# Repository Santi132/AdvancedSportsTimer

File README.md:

# AdvancedSportsTimer
Advanced Sports Timer, software code and hardware designs. As done by Santiago Gutierrez, Cristian Velasquez, and Patrick Tchassem

Published under GPLv3

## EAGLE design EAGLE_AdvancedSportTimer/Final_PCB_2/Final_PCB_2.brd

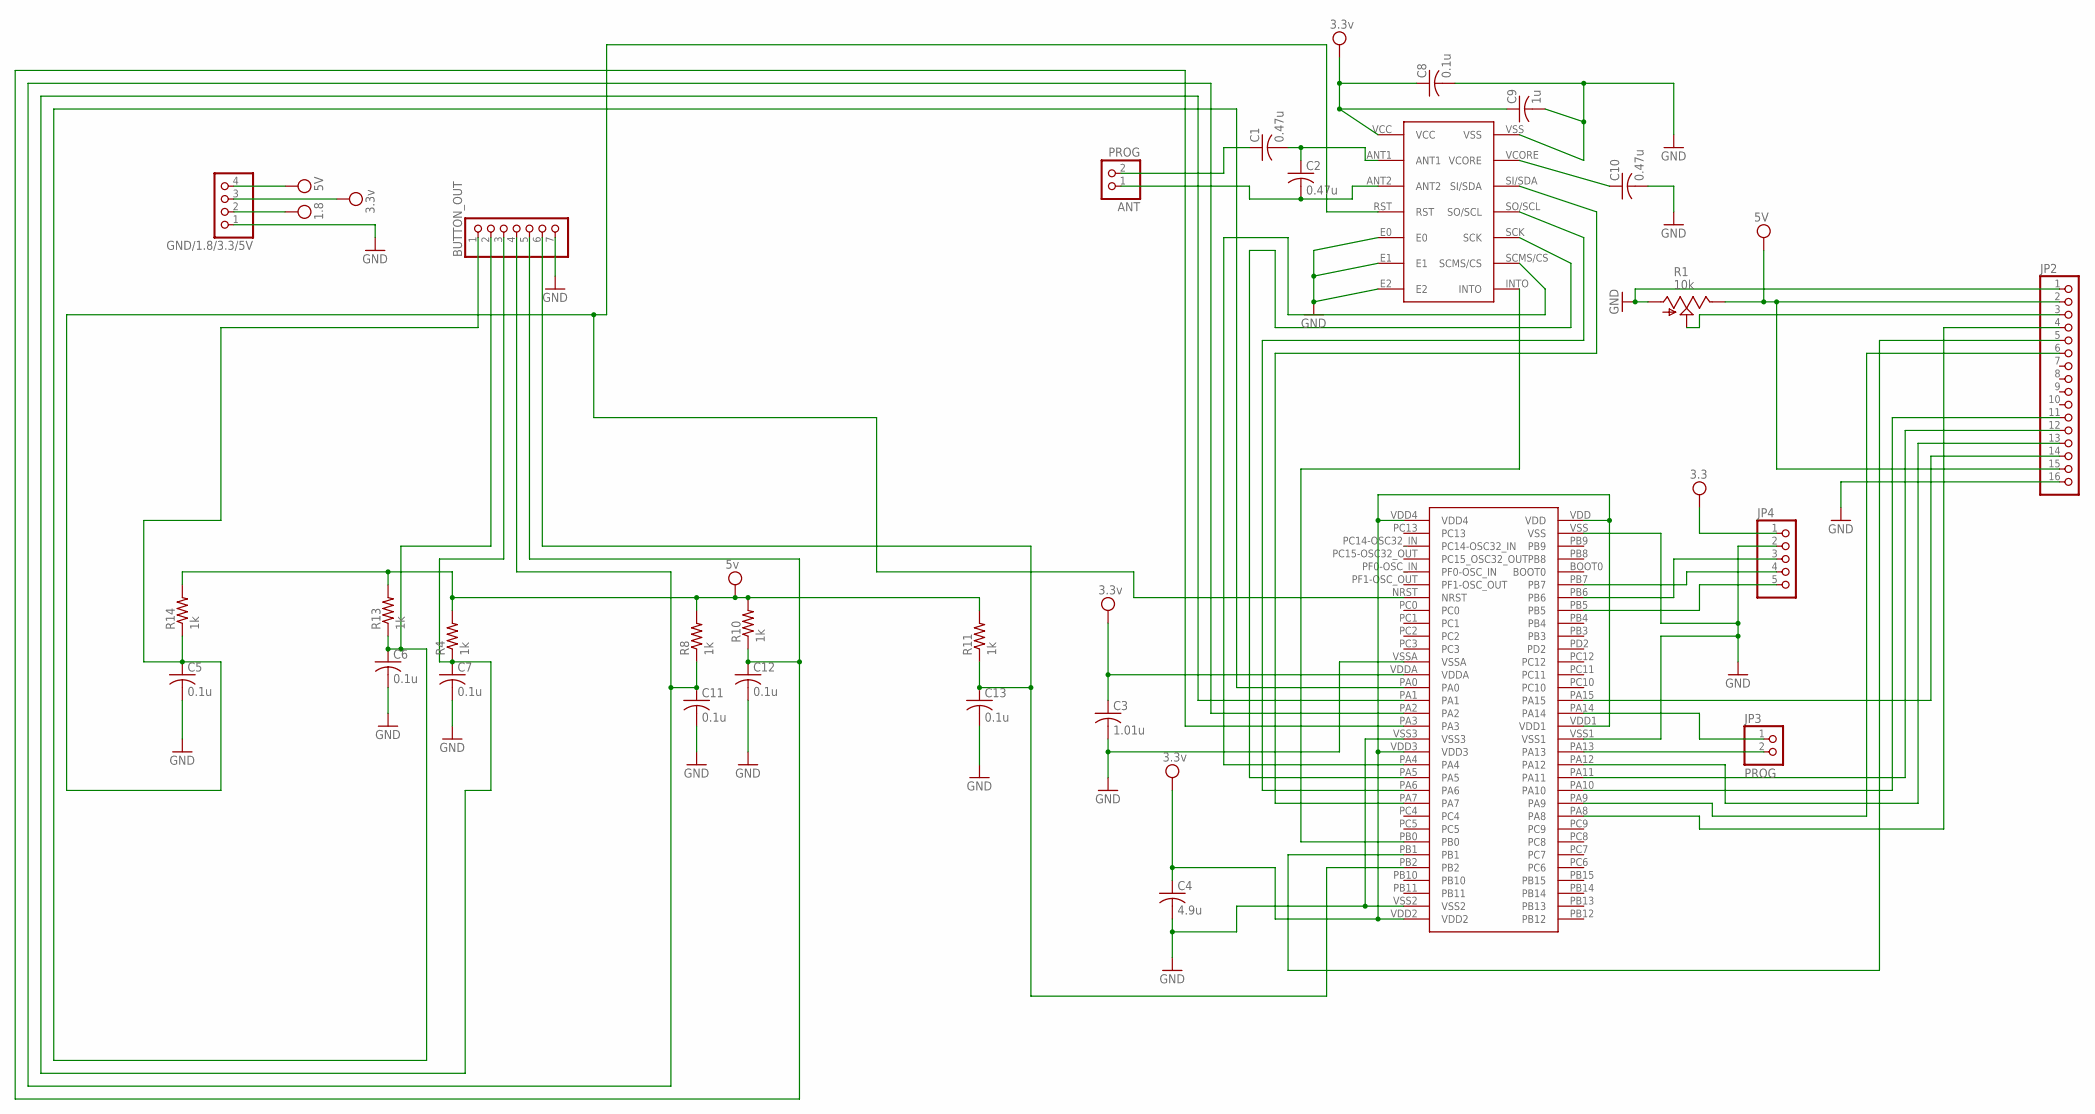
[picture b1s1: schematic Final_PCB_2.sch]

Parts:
ANT: PROG; 1X02
BUTTON_OUT: PINHD-1X7; 1X07
C1, C2, C10: 0.47u; C0805
C3: 1.01u; C0805
C4: 4.9u; C0805
C5, C6, C7, C8, C11, C12, C13: 0.1u; C0805
C9: 1u; C0805
GND/1.8/3.3/5V: PINHD-1X4/90; 1X04/90
JP2: PINHD-1X16; 1X16
JP3: PROG; 1X02
JP4: PINHD-1X5; 1X05
R1: 10k; B64Y
R4, R8, R10, R11, R13, R14: 1k; R0805
U$2: LQFP64
U$7: RF430CL330H

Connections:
GND: BUTTON_OUT.7, C3.2, C4.2, C5.2, C6.2, C7.2, C8.2, C9.2, C10.2, C11.2, C12.2, C13.2, GND/1.8/3.3/5V.1, JP2.1, JP2.16, JP4.2, R1.A, U$2.VSS, U$2.VSS1, U$2.VSS2, U$2.VSS3, U$2.VSSA, U$7.E0, U$7.E1, U$7.E2, U$7.VSS
unnamed: U$2.PB0, U$7.INTO
unnamed: U$2.PA5, U$7.SCK
unnamed: U$2.PA6, U$7.SO/SCL
unnamed: U$2.PA7, U$7.SI/SDA
unnamed: JP2.5, U$2.PB1
unnamed: ANT.1, C2.2, U$7.ANT2
unnamed: U$2.PA4, U$7.SCMS/CS
unnamed: C1.2, C2.1, U$7.ANT1
unnamed: BUTTON_OUT.3, C7.1, R4.1, U$2.PA1
unnamed: ANT.2, C1.1
unnamed: C10.1, U$7.VCORE
unnamed: JP2.3, R1.S
unnamed: JP2.4, U$2.PA8
unnamed: JP2.6, U$2.PA9
unnamed: JP2.11, U$2.PA10
unnamed: JP2.12, U$2.PA11
unnamed: JP2.13, U$2.PA12
unnamed: JP2.14, U$2.PA15
unnamed: BUTTON_OUT.5, C12.1, R10.1, U$2.PA3
unnamed: BUTTON_OUT.4, C11.1, R8.1, U$2.PA2
unnamed: JP3.1, U$2.PA14
unnamed: JP4.5, U$2.PB5
unnamed: JP4.3, U$2.PB6
unnamed: BUTTON_OUT.6, C13.1, R11.1, U$2.PB2
unnamed: BUTTON_OUT.1, C5.1, R14.1, U$2.NRST, U$7.RST
unnamed: BUTTON_OUT.2, C6.1, R13.1, U$2.PA0
unnamed: JP4.4, U$2.PB7
SWDIO: JP3.2, U$2.PA13
VCC: C3.1, C4.1, C8.1, C9.1, GND/1.8/3.3/5V.3, JP4.1, U$2.VDD, U$2.VDD1, U$2.VDD2, U$2.VDD3, U$2.VDD4, U$2.VDDA, U$7.VCC
VDD: GND/1.8/3.3/5V.4, JP2.2, JP2.15, R1.E, R4.2, R8.2, R10.2, R11.2, R13.2, R14.2
VEE: GND/1.8/3.3/5V.2

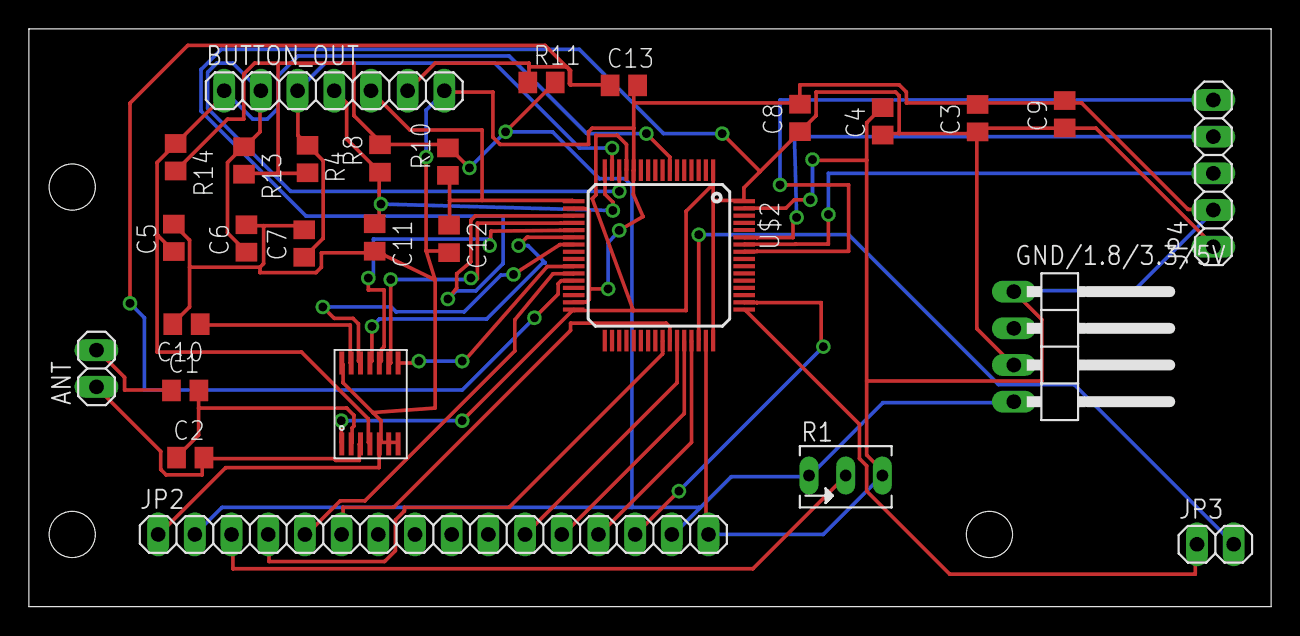
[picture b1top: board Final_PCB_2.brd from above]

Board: 2 copper layers, 86.0 x 40.0 mm, 28 parts (0 on the bottom side), 31 nets.

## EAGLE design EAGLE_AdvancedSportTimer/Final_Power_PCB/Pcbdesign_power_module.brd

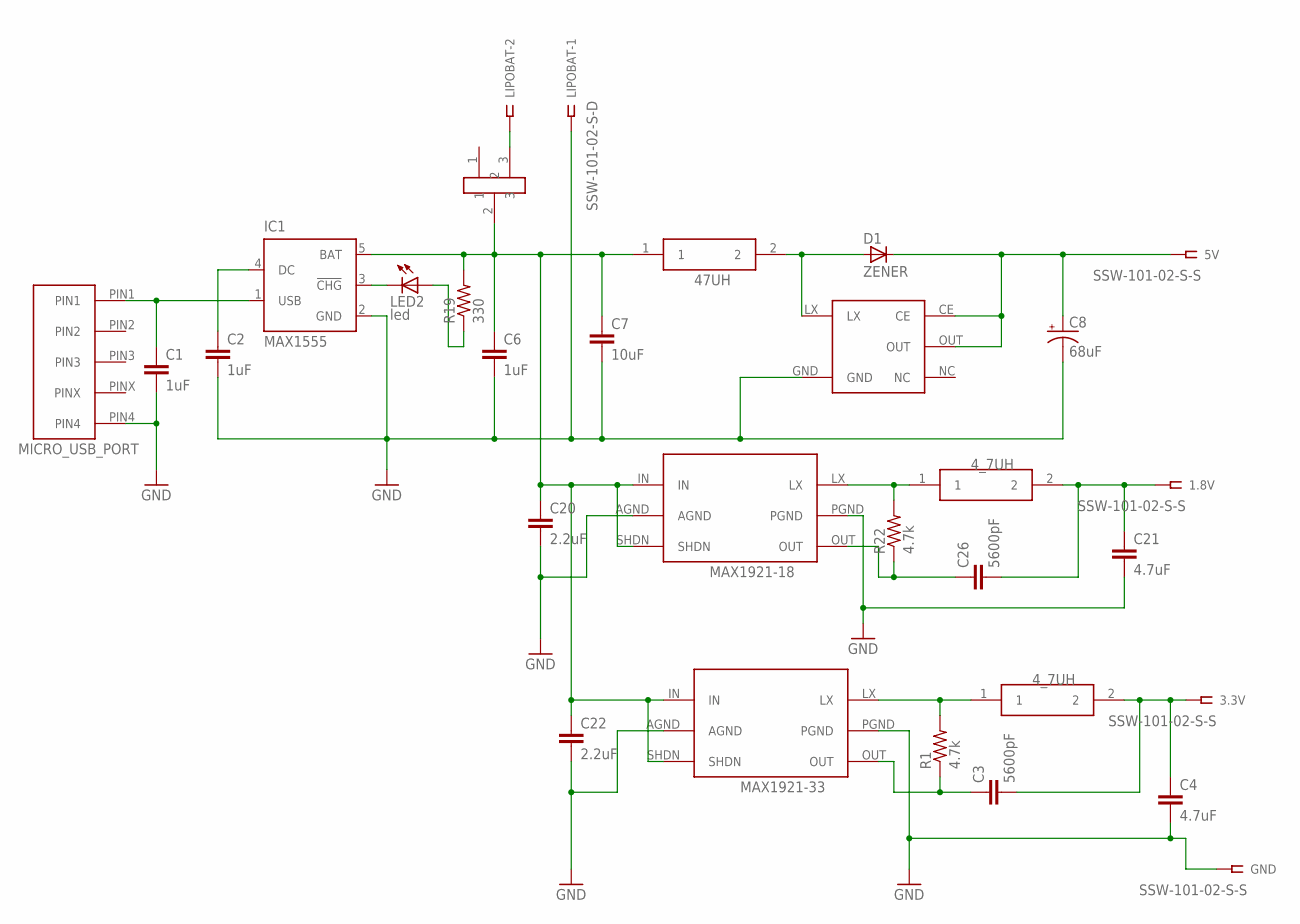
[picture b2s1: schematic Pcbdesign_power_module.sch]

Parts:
1.8V, 3.3V, 5V: SSW-101-02-S-S
10UH: SUMIDA_10U
C1, C2, C6: 1uF; C0805K
C3, C26: 5600pF; C0805K
C4, C21: 4.7uF; C0805K
C7: 10uF; C0805K
C8: 68uF; C/6032-28R
C20, C22: 2.2uF; C0805K
D1: ZENER; SOD123
GND: SSW-101-02-S-S
IC1: MAX1555; SOT23-5L
LED2: led; CHIPLED_0603
LIPOBAT: SSW-101-02-S-D
MAX1920, MAX1921-18: MAX1921
MICRO_USB: 10118192
R1, R22: 4.7k; R0805
R19: 330; R0805
U$1, U$2: SUMIDA_4.7U
U$3: NPC1402
U$4: SWITCH111

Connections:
GND: C1.2, C2.2, C4.2, C6.2, C7.2, C8.-, C20.2, C21.2, C22.2, GND.1, IC1.2 (GND), LIPOBAT.1, MAX1920.AGND, MAX1920.PGND, MAX1921-18.AGND, MAX1921-18.PGND, MICRO_USB.PIN4, U$3.GND
unnamed: C1.1, IC1.1 (USB), MICRO_USB.PIN1
unnamed: 5V.1, C8.+, D1.1 (C), U$3.CE, U$3.OUT
unnamed: IC1.3 (!CHG), LED2.C
unnamed: LED2.A, R19.1
unnamed: MAX1920.LX, R1.2, U$2.1
unnamed: LIPOBAT.2, U$4.3
unnamed: 1.8V.1, C21.1, C26.2, U$1.2
unnamed: MAX1921-18.LX, R22.2, U$1.1
unnamed: C26.1, MAX1921-18.OUT, R22.1
unnamed: 3.3V.1, C3.2, C4.1, U$2.2
unnamed: C3.1, MAX1920.OUT, R1.1
unnamed: 10UH.2, D1.2 (A), U$3.LX
unnamed: C2.1, IC1.4 (DC)
unnamed: 10UH.1, C6.1, C7.1, C20.1, C22.1, IC1.5 (BAT), MAX1920.IN, MAX1920.SHDN, MAX1921-18.IN, MAX1921-18.SHDN, R19.2, U$4.2

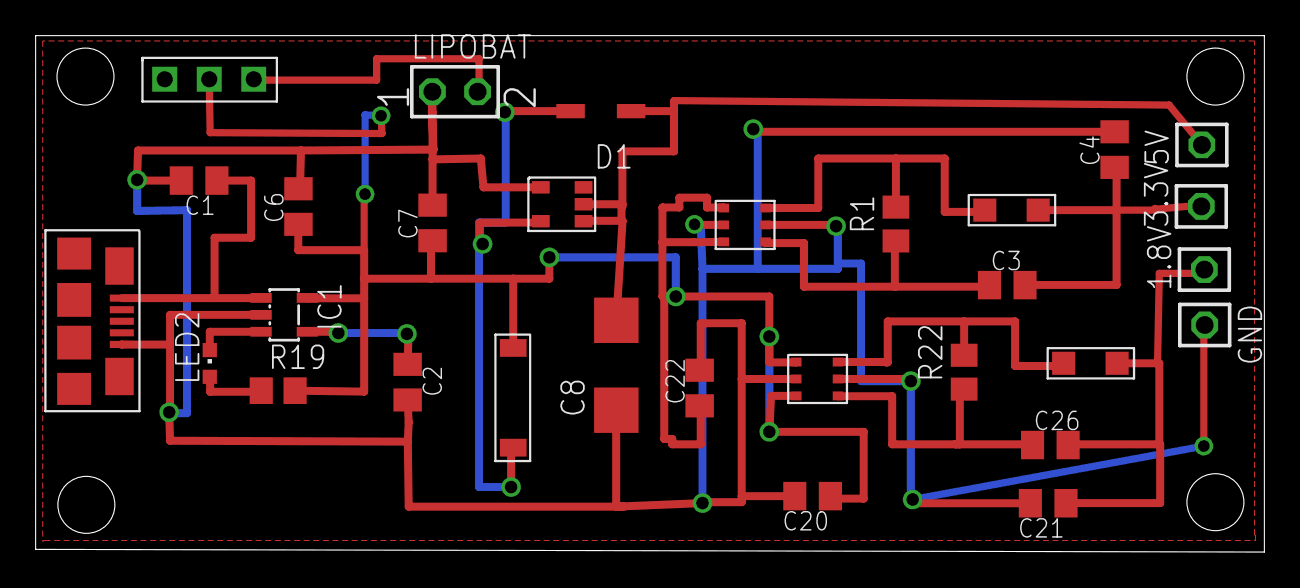
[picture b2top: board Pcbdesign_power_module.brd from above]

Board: 2 copper layers, 69.0 x 29.0 mm, 30 parts (0 on the bottom side), 15 nets.

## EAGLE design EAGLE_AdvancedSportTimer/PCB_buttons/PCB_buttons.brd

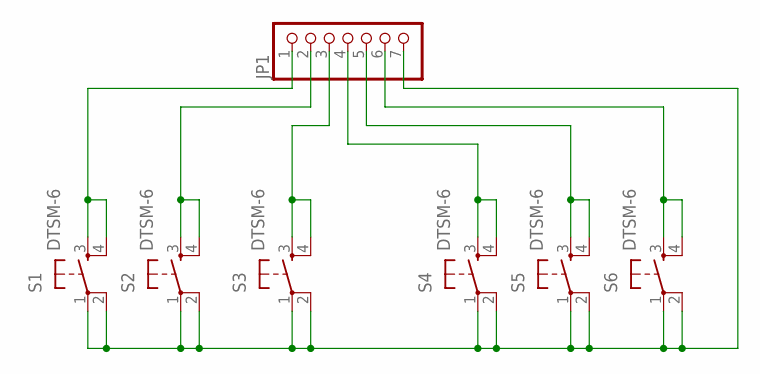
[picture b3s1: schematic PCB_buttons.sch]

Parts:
JP1: PINHD-1X7; 1X07
S1, S2, S3, S4, S5, S6: DTSM-6

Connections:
unnamed: JP1.7, S1.1, S1.2, S2.1, S2.2, S3.1, S3.2, S4.1, S4.2, S5.1, S5.2, S6.1, S6.2
unnamed: JP1.6, S6.3, S6.4
unnamed: JP1.5, S5.3, S5.4
unnamed: JP1.4, S4.3, S4.4
unnamed: JP1.3, S3.3, S3.4
unnamed: JP1.2, S2.3, S2.4
unnamed: JP1.1, S1.3, S1.4

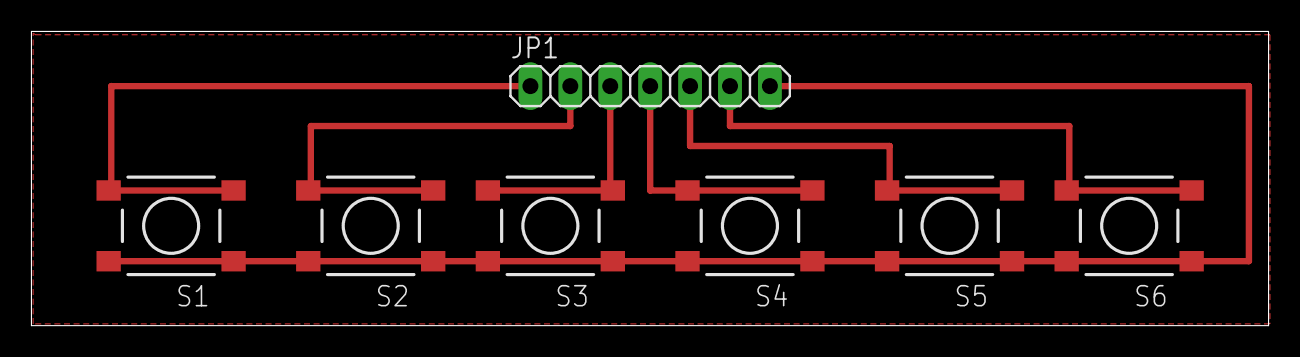
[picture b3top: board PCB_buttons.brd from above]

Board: 2 copper layers, 78.7 x 18.7 mm, 7 parts (0 on the bottom side), 7 nets.

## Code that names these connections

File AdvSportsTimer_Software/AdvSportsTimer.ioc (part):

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Mcu.Name=STM32F030RCTx
Mcu.Package=LQFP64
Mcu.UserName=STM32F030RCTx
PA10.Signal=GPIO_Output
PA11.Signal=GPIO_Output
PA12.Signal=GPIO_Output
PA13.Mode=Serial_Wire
PA13.Signal=SYS_SWDIO
PA14.Mode=Serial_Wire
PA14.Signal=SYS_SWCLK
PA15.Signal=GPIO_Output
PA8.Signal=GPIO_Output
PA9.Signal=GPIO_Output
PB1.Signal=GPIO_Output
board=AdvSportsTimer

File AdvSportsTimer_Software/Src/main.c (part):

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  HAL_GPIO_WritePin(GPIOA, GPIO_PIN_8|GPIO_PIN_9|GPIO_PIN_10|GPIO_PIN_11 
                          |GPIO_PIN_12|GPIO_PIN_15 | GPIO_PIN_4, GPIO_PIN_RESET);

  /*Configure GPIO pin : PB1 */
  GPIO_InitStruct.Pin = GPIO_PIN_1;
  GPIO_InitStruct.Mode = GPIO_MODE_OUTPUT_PP;
  GPIO_InitStruct.Pull = GPIO_NOPULL;
  GPIO_InitStruct.Speed = GPIO_SPEED_FREQ_HIGH;
  HAL_GPIO_Init(GPIOB, &GPIO_InitStruct);
	
	/*Configure GPIO pin : PB0 */
  GPIO_InitStruct.Pin = GPIO_PIN_0;
  GPIO_InitStruct.Mode = GPIO_MODE_INPUT;
  GPIO_InitStruct.Pull = GPIO_NOPULL;
  HAL_GPIO_Init(GPIOB, &GPIO_InitStruct);

  /*Configure GPIO pins : PA8 PA9 PA10 PA11 
                           PA12 PA15 PA4 */
  GPIO_InitStruct.Pin = GPIO_PIN_4 | GPIO_PIN_8|GPIO_PIN_9|GPIO_PIN_10|GPIO_PIN_11 
                          |GPIO_PIN_12|GPIO_PIN_15;
  GPIO_InitStruct.Mode = GPIO_MODE_OUTPUT_PP;
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
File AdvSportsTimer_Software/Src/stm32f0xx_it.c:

/**
  ******************************************************************************
  * @file    stm32f0xx_it.c
  * @brief   Interrupt Service Routines.
  ******************************************************************************
  *
  * COPYRIGHT(c) 2017 STMicroelectronics
  *
  * Redistribution and use in source and binary forms, with or without modification,
  * are permitted provided that the following conditions are met:
  *   1. Redistributions of source code must retain the above copyright notice,
  *      this list of conditions and the following disclaimer.
  *   2. Redistributions in binary form must reproduce the above copyright notice,
  *      this list of conditions and the following disclaimer in the documentation
  *      and/or other materials provided with the distribution.
  *   3. Neither the name of STMicroelectronics nor the names of its contributors
  *      may be used to endorse or promote products derived from this software
  *      without specific prior written permission.
  *
  * THIS SOFTWARE IS PROVIDED BY THE COPYRIGHT HOLDERS AND CONTRIBUTORS "AS IS"
  * AND ANY EXPRESS OR IMPLIED WARRANTIES, INCLUDING, BUT NOT LIMITED TO, THE
  * IMPLIED WARRANTIES OF MERCHANTABILITY AND FITNESS FOR A PARTICULAR PURPOSE ARE
  * DISCLAIMED. IN NO EVENT SHALL THE COPYRIGHT HOLDER OR CONTRIBUTORS BE LIABLE
  * FOR ANY DIRECT, INDIRECT, INCIDENTAL, SPECIAL, EXEMPLARY, OR CONSEQUENTIAL
  * DAMAGES (INCLUDING, BUT NOT LIMITED TO, PROCUREMENT OF SUBSTITUTE GOODS OR
  * SERVICES; LOSS OF USE, DATA, OR PROFITS; OR BUSINESS INTERRUPTION) HOWEVER
  * CAUSED AND ON ANY THEORY OF LIABILITY, WHETHER IN CONTRACT, STRICT LIABILITY,
  * OR TORT (INCLUDING NEGLIGENCE OR OTHERWISE) ARISING IN ANY WAY OUT OF THE USE
  * OF THIS SOFTWARE, EVEN IF ADVISED OF THE POSSIBILITY OF SUCH DAMAGE.
  *
  ******************************************************************************
  */
/* Includes ------------------------------------------------------------------*/
#include "stm32f0xx_hal.h"
#include "stm32f0xx.h"
#include "stm32f0xx_it.h"

/* USER CODE BEGIN 0 */

/* USER CODE END 0 */

/* External variables --------------------------------------------------------*/
volatile unsigned int Milliseconds, Seconds, Minutes;
volatile unsigned int start;
volatile unsigned int lap_flag, lap_ms, lap_sec, lap_min;
Mode timer_mode = NORMAL;
volatile unsigned int clear_screen_flag, time_up_flag;

/******************************************************************************/
/*            Cortex-M0 Processor Interruption and Exception Handlers         */ 
/******************************************************************************/

/**
* @brief This function handles Non maskable interrupt.
*/
void NMI_Handler(void)
{
  /* USER CODE BEGIN NonMaskableInt_IRQn 0 */

  /* USER CODE END NonMaskableInt_IRQn 0 */
  /* USER CODE BEGIN NonMaskableInt_IRQn 1 */

  /* USER CODE END NonMaskableInt_IRQn 1 */
}

/**
* @brief This function handles Hard fault interrupt.
*/
void HardFault_Handler(void)
{
  /* USER CODE BEGIN HardFault_IRQn 0 */

  /* USER CODE END HardFault_IRQn 0 */
  while (1)
  {
  }
  /* USER CODE BEGIN HardFault_IRQn 1 */

  /* USER CODE END HardFault_IRQn 1 */
}

/**
* @brief This function handles System service call via SWI instruction.
*/
void SVC_Handler(void)
{
  /* USER CODE BEGIN SVC_IRQn 0 */

  /* USER CODE END SVC_IRQn 0 */
  /* USER CODE BEGIN SVC_IRQn 1 */

  /* USER CODE END SVC_IRQn 1 */
}

/**
* @brief This function handles Pendable request for system service.
*/
void PendSV_Handler(void)
{
  /* USER CODE BEGIN PendSV_IRQn 0 */

  /* USER CODE END PendSV_IRQn 0 */
  /* USER CODE BEGIN PendSV_IRQn 1 */

  /* USER CODE END PendSV_IRQn 1 */
}

/**
* @brief This function handles System tick timer.
*/
void SysTick_Handler(void)
{
	if(start){
		if(timer_mode){
			if(Milliseconds == 0){
				if(Seconds == 0){
					//Out of seconds
					if(Minutes == 0){
						//Times up
						time_up_flag = 1;
						start = 0;
					}
					else{
						Minutes--;
						Seconds = 59;
					}
				}
				else{
					//still have some seconds
					Seconds--;
					Milliseconds = 999;
				}
			}
			else{
				Milliseconds--;
			}
		}
		else{
			Milliseconds++;
			if(Milliseconds == 1000){
				Seconds++;
				Milliseconds = 0;
			}
			if(Seconds == 60){
				Minutes++;
				Seconds = 0;
			} 
			if(Minutes == 60){
				Minutes = 0;
			}
		}
	}
	
  HAL_IncTick();
  HAL_SYSTICK_IRQHandler();
  /* USER CODE BEGIN SysTick_IRQn 1 */

  /* USER CODE END SysTick_IRQn 1 */
}

/******************************************************************************/
/* STM32F0xx Peripheral Interrupt Handlers                                    */
/* Add here the Interrupt Handlers for the used peripherals.                  */
/* For the available peripheral interrupt handler names,                      */
/* please refer to the startup file (startup_stm32f0xx.s).                    */
/******************************************************************************/

/* USER CODE BEGIN 1 */
void EXTI2_3_IRQHandler(void){
	//check to see if the correct line was triggered
	if((EXTI->IMR & EXTI_IMR_MR2) && (EXTI->PR & EXTI_PR_PR2)){
		//PA2 was triggered
		if(start){
			start = 0; //STOP
			lap_flag = 0;
			lap_min = 0;
			lap_sec = 0;
			lap_ms = 0;
		}
		else{
			start = 1; //START
			clear_screen_flag = 1;
		}
		while(GPIOA->IDR & GPIO_IDR_2){}
		EXTI->PR |= EXTI_PR_PR2;
	}
	else{
		//PA3 was triggered
		if(timer_mode){
			//were in COUNTDOWN mode
			if(Seconds > 30){
				Minutes++;
				Seconds = Seconds - 30;
			}
			else{
				Seconds += 30;
				if(Seconds == 60){
					Minutes++;
					Seconds = 0;
				}
			}
		}
		else{	
			lap_flag = 1;
			lap_min = Minutes;
			lap_sec = Seconds;
			lap_ms = Milliseconds;
		}
		while(GPIOA->IDR & GPIO_IDR_3){}
		EXTI->PR |= EXTI_PR_PR3;
	}
}

void EXTI0_1_IRQHandler(void){
	if((EXTI->IMR & EXTI_IMR_MR0) && (EXTI->PR & EXTI_PR_PR0)){
		//PA0 was triggered change the mode
		if(timer_mode){ //is it in COUNTDOWN mode
			//right now there is only two modes, might add some later
			timer_mode = NORMAL;
		}
		else{
			timer_mode = COUNTDOWN;
		}
		Minutes = 0;
		Seconds = 0;
		Milliseconds = 0;
		clear_screen_flag = 1;
		while(GPIOA->IDR & GPIO_IDR_0){}
		EXTI->PR |= EXTI_PR_PR0;
	}
	else{
		//PA1 was triggered
		//show heartbeat?
		if(timer_mode){
			//COUNTDOWN mode
			if(Seconds < 30){
				if(Minutes != 0){
					Minutes--;
					Seconds = 30 + Seconds;
				}
			}
			else{
				Seconds -= 30;
			}
		}
		while(GPIOA->IDR & GPIO_IDR_1){}
		EXTI->PR |= EXTI_PR_PR1;
	}
}
/* USER CODE END 1 */
/************************ (C) COPYRIGHT STMicroelectronics *****END OF FILE****/

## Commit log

2017-05-12 Adding in all necessary files
